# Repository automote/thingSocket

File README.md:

# thingSocket
__thingSocket__ is a Wi-Fi enabled socket/plug coupled with open APIs for people to develop, deploy or even clone.

__thingSocket__ is an attempt to promote IoT by providing open and hackable devices that you use everyday. Devices like bulbs, sockets, presence detectors and many more. The idea revolves around identifying frequently accessed devices and converting them into IoT devices by adding Wi-Fi, BLE or ZigBee capabilities.

We are starting with a Wi-Fi Socket and a Wi-Fi Bulb. These devices have the crowd favourite ESP8266 modules and we are planning to keep the hardware and software design open. This would encourage school and college students and even IoT enthusiasts to get into the IoT Bandwagon.

## Software
The software is completely written in __Arduino IDE__, so anyone familiar with the IDE can tinker with the code and personalise the device according to his taste.
The Algorithmic flow chart is mentioned below:
<p align="center">

The sketch will search for SSID and Password in EEPROM and tries to connect to the AP using the SSID and Password. If it fails then it boots into AP mode and asks for SSID and Password from the user. Connect to the thingSocket using the following: (SSID = thingSocket-<last 3 digits of MAC> and PASSWORD = 12345678)

While in __AP__ mode SSID and Password shoud be given using the following API. A webpage is also provided for entering SSID and Password if you are using the browser method.
- http://192.168.4.1/a?ssid="yourSSID"&pass="yourPSKkey"

The ESP in thingSocket acts as Webserver on port 80 and has the following __APIs__

The server will set a GPIO14 pin depending on the request
 - http://server_ip/plug/read will read all the plug status,
 - http://server_ip/plug/on will set the GPIO14 low,
 - http://server_ip/plug/off will set the GPIO14 high

Other functionality include
- http://server_ip/factoryreset will clear the EEPROM contents. Its serves the purpose of factory resetting the device
- http://server_ip/reboot will reboot the device after 10 seconds
- http://server_ip/setappliance will set the appliance location, type and name

where <I>server_ip</I> is the IP address of the ESP8266 module, will be printed to Serial when the module is connected.
- v0.5 is the standalone version
- v0.6 is currently developed version
- other sketches are the modules which were used in the v0.5 and v0.6
- v0.7 is in development which makes use of Wi-Fi Manager by <i>tzapu</i> https://github.com/tzapu/WiFiManager

## Hardware
The hardware is kept simple and has been designed in Eagle for anyone to use the schematic and board files to develop his own product. We are even planing to provide __GERBER__ files once we ready with the Design. 

- For Geeks, they can directly buy the hardware from us or can make their own device
- For Tinkerers, UART pins are provided to flash the code of their choice or improve upon the already existing code
- For ESP Extremists, they can flash NodeMCU firmware and start coding in Lua. Example codes will be provided soon

### Bugs
Code contains bugs some of which are critical while others are non critical
- Critical:
  - ~~while submitting the SSID and password the URL doesnot encode spacial characters~~
  - PLUG status is not stored in case of power cut
  - PLUG will remain off on restart
  - After reboot broadcast and multicast packets have decreased length
  - Watchdog timer setup to reset device if its in loop
  - thingSocket not rebooting properly after connection lost with router
   
- Non-Critical:
  - Previous SSID and password still remains in memory even after factory reset
  - ~~multicast packets are not broken into separate packets~~
  - ~~string of appl_type is not getting parsed properly~~
  - ~~AP mode remains on in STA mode as well~~

#### Inspiration
- http://www.esp8266.com/viewtopic.php?f=29&t=2520

#### Alpha Version
  - Alpha version is available for testing and verification
People who are interested can contact Lovelesh: lovelesh06101990@gmail.com

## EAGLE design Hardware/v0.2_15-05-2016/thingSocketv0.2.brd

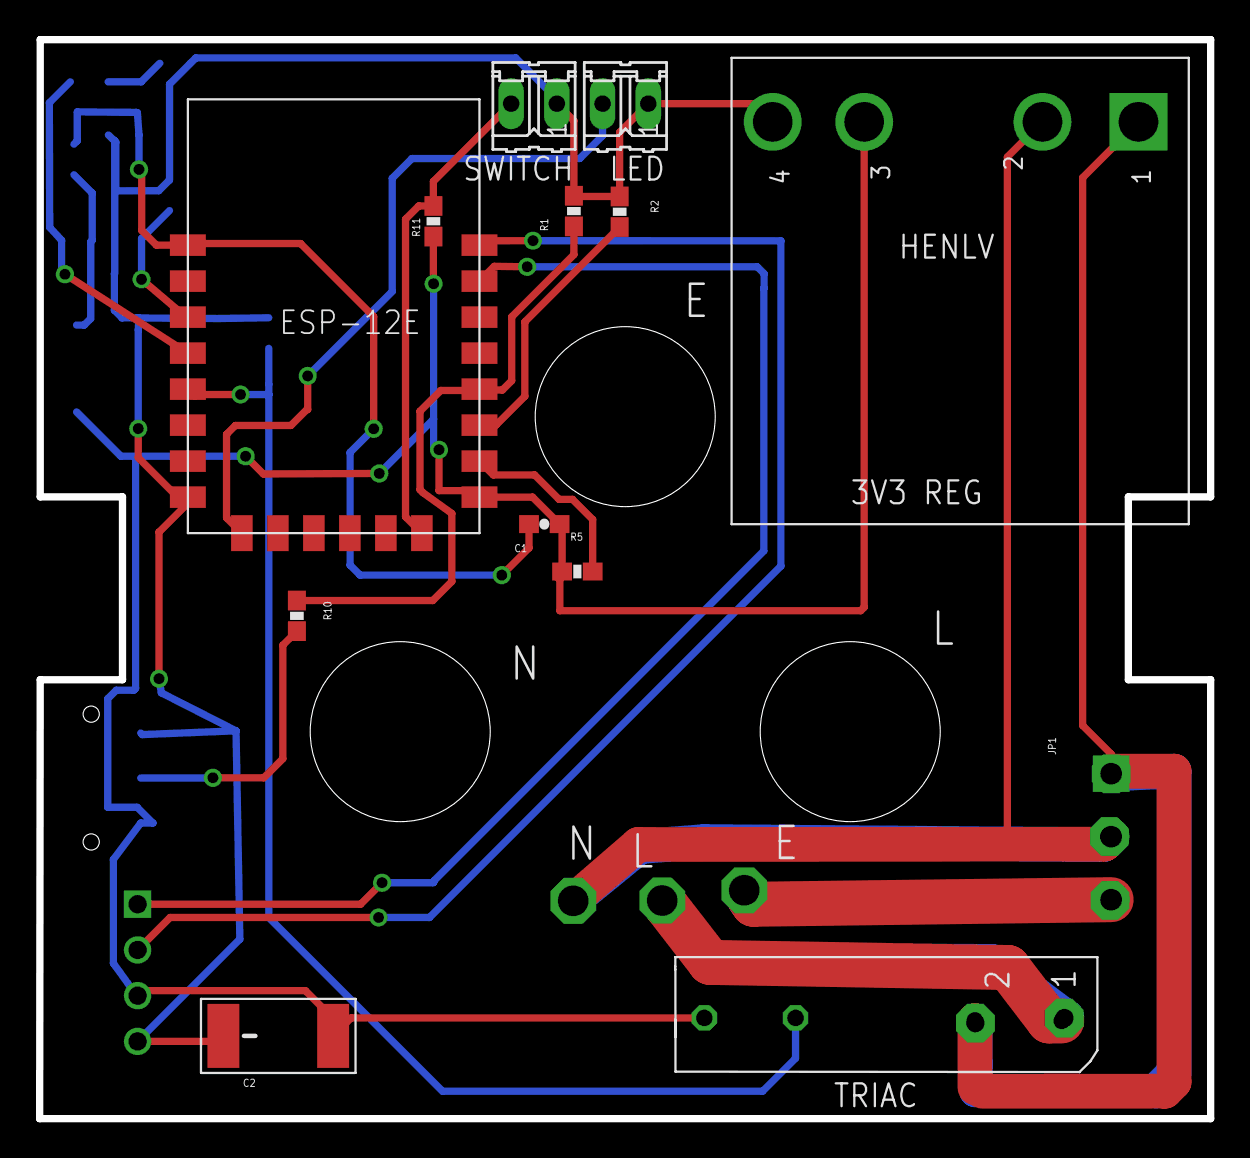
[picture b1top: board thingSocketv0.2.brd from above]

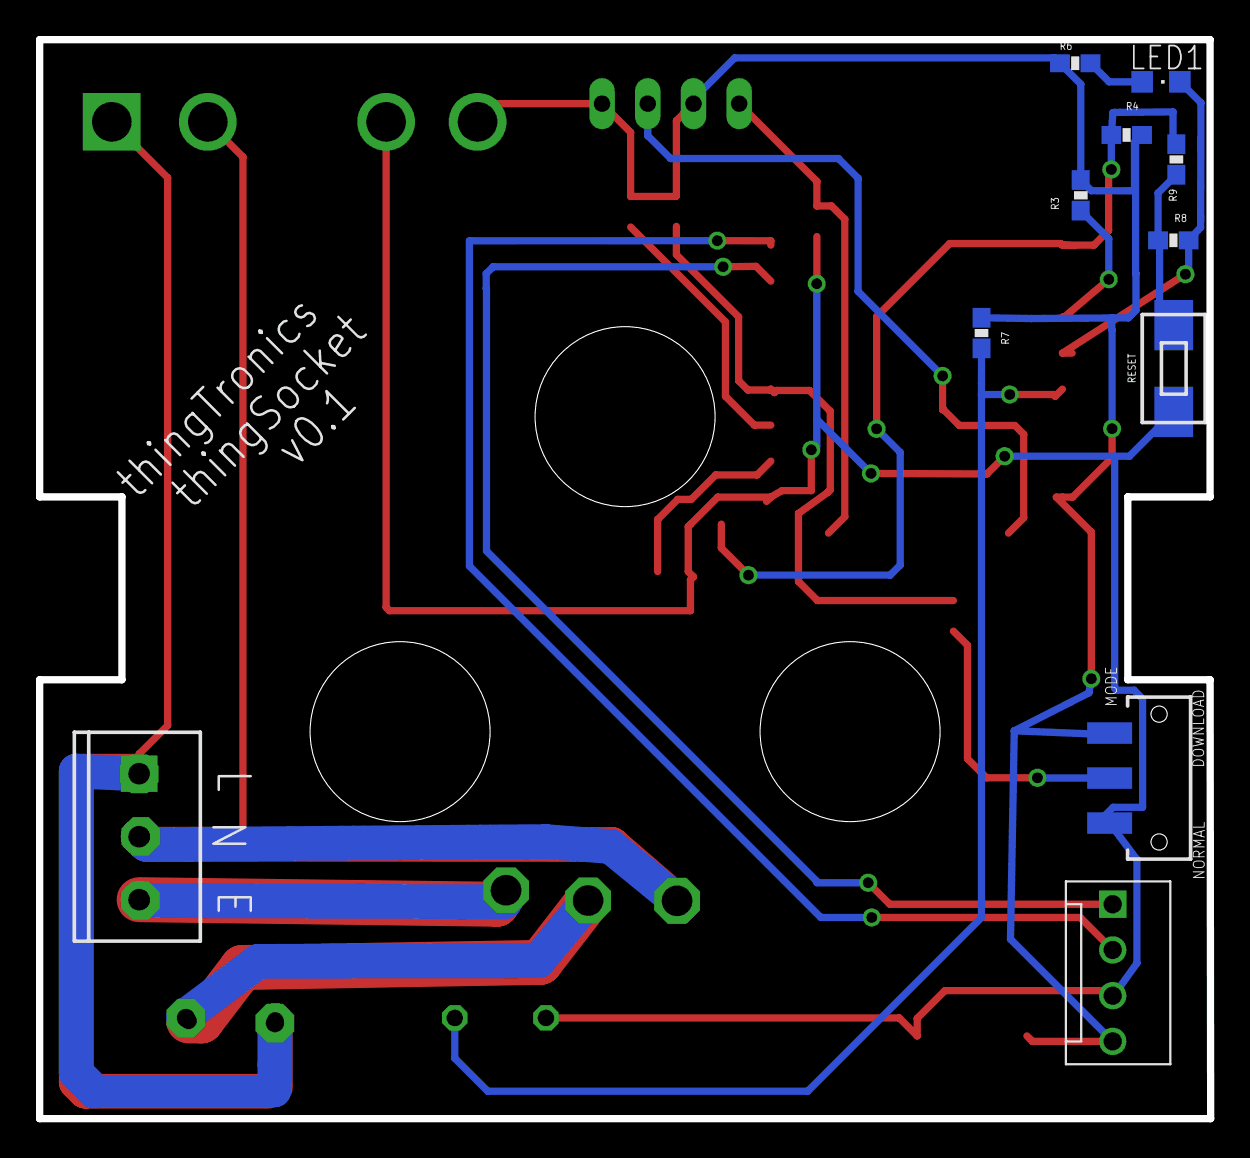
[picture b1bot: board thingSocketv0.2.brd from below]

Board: 2 copper layers, 65.1 x 59.9 mm, 35 parts (11 on the bottom side), 24 nets.

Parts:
4PINHEADER: OUPIIN-4071V-4
C1: 1uf; 0603-CAP
C2: 0.1uf; VISHAY_C
DRILEGEND: DRILEGEND
HENLV: 3V3 REG; HENLV3.3PKG
JP1: SCREWTERMINAL-3.5MM-3
LED: 02P
LED1: CHIPLED_0805
MDL1: ESP8266-ESP12E
MODE: SWITCH-SPDT-SMD
R1, R2, R3, R4, R5, R7, R10: 12k; 0603-RES
R6, R9: 470e; 0603-RES
R8: NC; 0603-RES
R11: 10k; 0603-RES
RESET: TL3303_J
SWITCH: 02P
TP1, TP2, TP3: TPPAD1-17; P1-17
TP4, TP5, TP6, TP7, TP8, TP9, TP10, TP11: TP-040
TRIAC: JP2Q

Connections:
3.3V: 4PINHEADER.4, C2.+, HENLV.4, LED.1, MDL1.8, MODE.1, R1.1, R2.1, R3.1, R4.1, R6.1, R7.1, SWITCH.1
APPLI: TP1.1, TRIAC.1
CH_PD: MDL1.3, R3.2
EARTH: JP1.3, TP3.1
GND: 4PINHEADER.3, C1.2, C2.-, HENLV.3, MDL1.9, MODE.3, R5.1, R11.1, RESET.2, TRIAC.4
GPIO0: MDL1.12, R1.2, R10.1
GPIO2: MDL1.11, R2.2
GPIO9: LED.2, MDL1.18
GPIO10: MDL1.20, R11.2, SWITCH.2
GPIO14: MDL1.5, R7.2, TRIAC.3
GPIO15: MDL1.10, R5.2
GPIO16: LED1.C, MDL1.4, R8.2
L: HENLV.1, JP1.1, TRIAC.2
N: HENLV.2, JP1.2, TP2.1
unnamed: TP4.1, TP5.1
unnamed: TP6.1, TP7.1
unnamed: R8.1, R9.1, RESET.1
unnamed: TP8.1, TP9.1
unnamed: TP10.1, TP11.1
unnamed: MODE.2, R10.2
unnamed: LED1.A, R6.2
REST: C1.1, MDL1.1, R4.2, R9.2
RXD: 4PINHEADER.1, MDL1.15
TXD: 4PINHEADER.2, MDL1.16

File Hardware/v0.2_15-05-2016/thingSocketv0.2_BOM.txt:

Partlist exported from P:/Arduino-sketches/thingSocket/Hardware/v0.2_15-05-2016/thingSocketv0.2.sch at 24-10-2016 13:41

Qty Value     Device                    Package               Parts                                    Description                                             
1             ESP8266-12EESP8266-ESP12E ESP8266-ESP12E        MDL1                                     ESP8266-12E with additional I/O and GPIO04/05 corrected 
1             JP2Q                      JP2Q                  TRIAC                                    JUMPER                                                  
1             LEDCHIPLED_0805           CHIPLED_0805          LED1                                     LED                                                     
2             M02                       02P                   LED, SWITCH                              AMP QUICK CONNECTOR                                     
1             M03SCREW                  SCREWTERMINAL-3.5MM-3 JP1                                      Header 3                                                
1             M04-V                     OUPIIN-4071V-4        PROG                                     Oupiin 4071 Series: 4 Pin Male                          
1             SWITCH-SPSTSMD2           SWITCH-SPDT-SMD       MODE                                     SPST Switch                                             
1             TL3302-J                  TL3303_J              RESET                                    E-Switch TL3302 Series Tactile Switch                   
1   0.1uf     CAP_POLSMD                VISHAY_C              C2                                       Capacitor Polarized                                     
6   12k       RESISTOR0805-RES          00805-RES             R1, R2, R3, R4, R5, R7                   Resistor                                                
1   1uf       CAP0805-CAP               0805-CAP              C1                                       Capacitor                                               
1   3V3 REG   HENLV3.3                  HENLV3.3PKG           HENLV                                    JUMPER                                                  
2   470e      RESISTOR0805-RES          0805-RES              R6, R9                                   Resistor                                                
1   NC        RESISTOR0805-RES          0805-RES              R8                                       Resistor                                                
8   TP-040    TP-040                    TP-040                TP4, TP5, TP6, TP7, TP8, TP9, TP10, TP11 TEST POINT                                              
3   TPPAD1-17 TPPAD1-17                 P1-17                 TP1, TP2, TP3                            Test pad

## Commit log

2016-01-07 :circus_tent: Added .gitattributes & .gitignore files
2016-01-07 Created Readme file
2016-01-07 added smart-plugv0.5
2016-01-08 pre-production code ready
2016-01-08 edited README.md
2016-01-08 adding documentation to README and ino file
2016-01-08 edited README.md and minor modifications to smart-plug
2016-01-08 added rebooting feature on connection drop
2016-01-09 minor changes
2016-01-09 added new brdcast and notif msg string
2016-01-09 edited the v0.5
2016-01-09 regular cleanup of repo
2016-01-10 added zone, appl_type, appl_name to v0.6
2016-01-12 added mDNS service
2016-01-12 working on twin multicasts packets and substring
2016-01-14 added author name to codes
2016-02-04 added hardware folder and minor changes to code
2016-02-04 added necessary changes to v0.5, v0.6, v0.7
2016-02-04 added date to hardware files
2016-02-07 changed brdcast and notif ports and the strings modified
2016-02-10 added dev images and edited readme.md
2016-02-10 added modificaions to readme.md
2016-02-16 added thingSocketv1.0 and changes to readme.md
2016-02-16 adding support for switch and LED in thingSocketv1.0
2016-02-17 product ready software version ready
2016-02-18 removed unwanted sketches
2016-02-18 removed extra sketches
2016-02-18 removes extra sketches
2016-02-19 made some changes to 1.1
2016-02-20 send all reference to new folder
2016-02-26 minor changes to the notif service
2016-03-03 edited broadcast and notification msg + included mac addition to device name
2016-03-03 code cleanup
2016-03-04 added APpsk
2016-03-15 restored v1.0 to orignal version
2016-03-18 code tested on thingSocket hardware
2016-03-23 changes READ response to ON:OFF instead of 1:0
2016-03-25 added version no to all files; removes rar files
2016-03-25 will ignore .zip and .rar files from now on
2016-03-26 added critical restart issue in readme
2016-05-15 version 0.2 started
2016-10-16 unified the resource mechanism; added device password
2016-10-17 v2.0 drafted
2016-10-17 added #ifdef DEBUG statements
2016-10-21 removed the update bug.
2016-10-21 minor bug fixes
2016-11-02 added default mechanism for factory reset
2016-11-04 minor correction to the PLUG GPIO
2017-07-03 Updated hardware directory structure
2017-07-03 power and current measuring section done
2017-07-14 renamed the hardware version to v2.0; made a separate folder for v2.0 software version
2017-07-14 updated the name to POW

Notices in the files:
parts and their libraries:
SparkFun-Capacitors: Licensing: Creative Commons ShareAlike 4.0 International - https://creativecommons.org/licenses/by-sa/4.0
